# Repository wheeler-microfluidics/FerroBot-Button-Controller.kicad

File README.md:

# FerroBot-Button-Controller.kicad
To control the ferrobot ((https://github.com/wheeler-microfluidics/FerroBot). Firmware here: https://github.com/wheeler-microfluidics/FerroBot-Button-Controller.ino/tree/master

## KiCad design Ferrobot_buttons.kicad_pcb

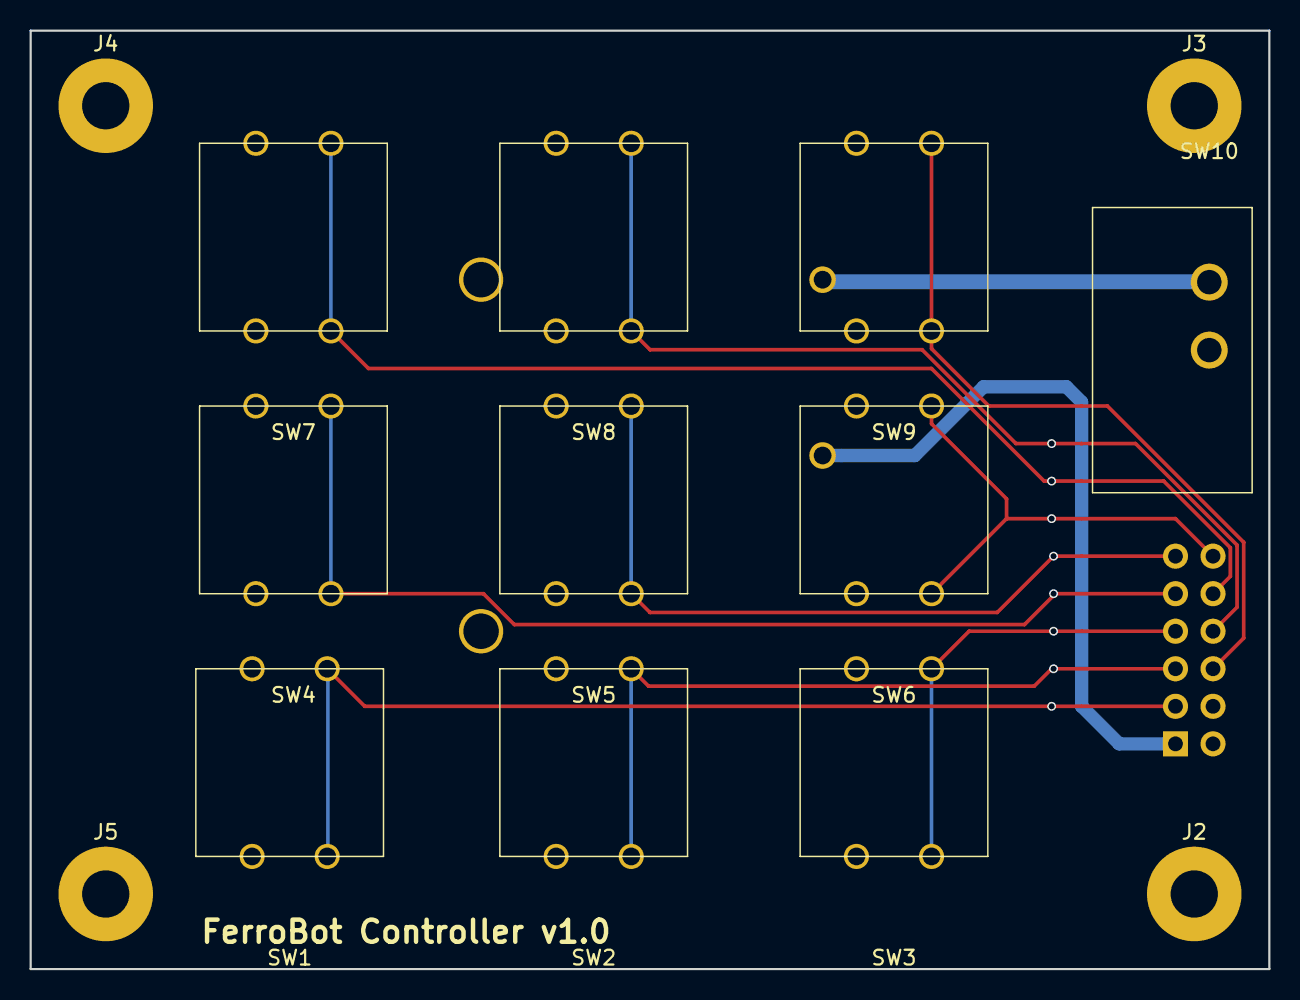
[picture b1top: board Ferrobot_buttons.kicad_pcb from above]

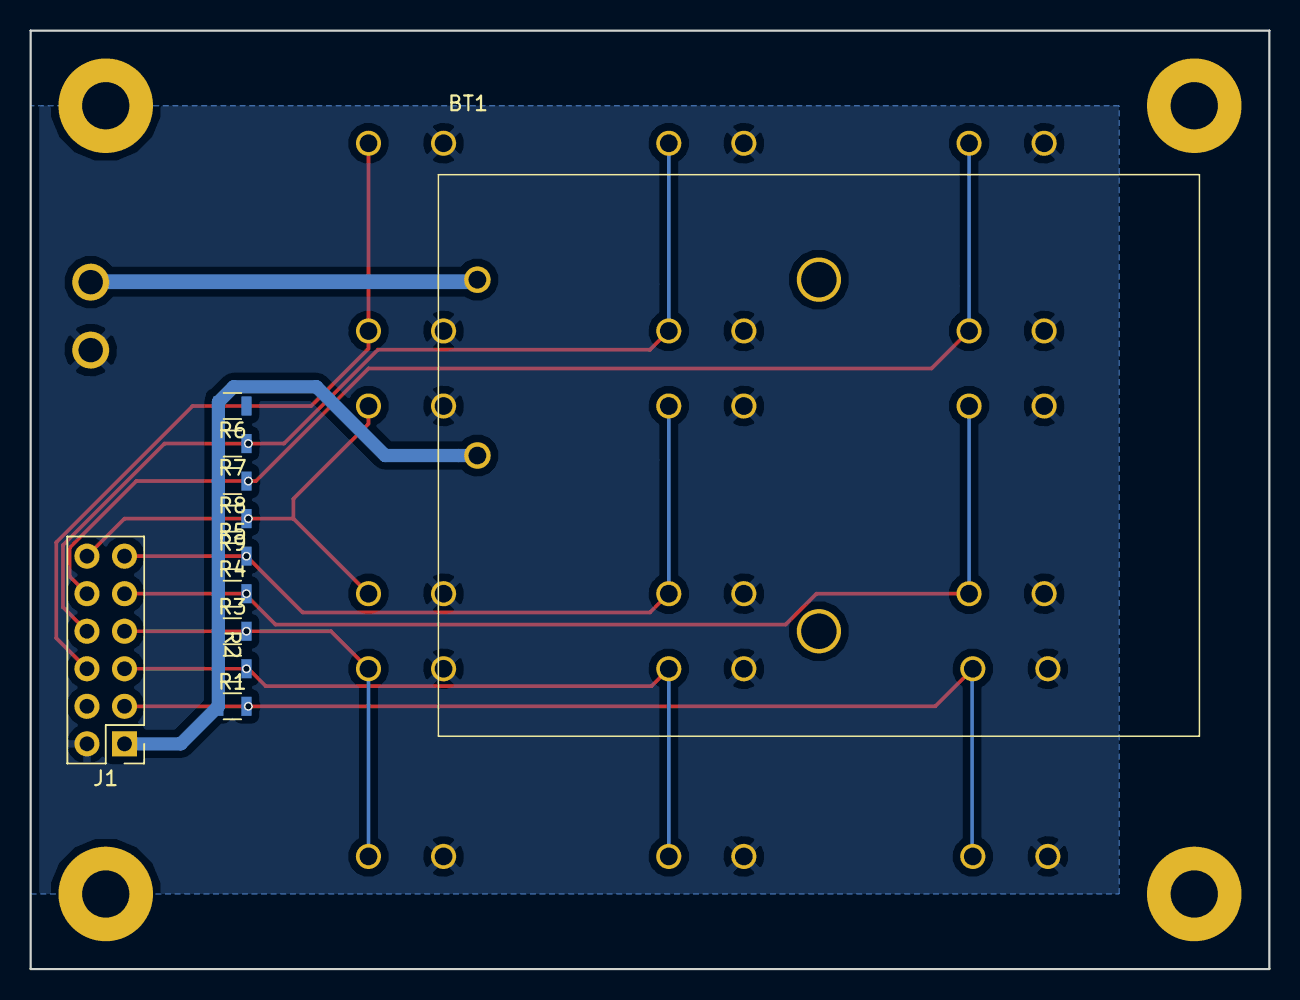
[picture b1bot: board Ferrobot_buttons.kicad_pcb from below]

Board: 2 copper layers, 83.8 x 63.5 mm, 25 parts (11 on the bottom side), 12 nets.

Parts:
BT1: Battery; THREE_AAA_BATTERY_HOLDER
J1: CONN_02X06; Pin_Header_Straight_2x06_Pitch2.54mm
J2, J3, J4, J5: CONN_01X01; MountingHole_3.2mm_M3_Pad
R1, R2, R3, R4, R5, R6, R7, R8, R9: 10k; R_0805
SW1, SW2, SW3, SW4, SW5, SW6, SW7, SW8, SW9: Button; ADAFRUIT_SQUARE_BUTTON
SW10: SW_DIP_x01; L101_Switch

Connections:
BATTERY_OUT: BT1.1, SW10.1
GND: BT1.2, J1.1, R1.1, R2.1, R3.1, R4.1, R5.1, R6.2, R7.2, R8.2, R9.2
MAGNET1: J1.3, R1.2, SW1.2, SW1.4
MAGNET2: J1.5, R2.2, SW2.2, SW2.4
MAGNET3: J1.7, R3.2, SW3.2, SW3.4
MAGNET4: J1.9, R4.2, SW4.2, SW4.4
MAGNET5: J1.11, R5.2, SW5.2, SW5.4
MAGNET6: J1.12, R9.1, SW6.2, SW6.4
MAGNET7: J1.10, R8.1, SW7.2, SW7.4
MAGNET8: J1.8, R7.1, SW8.2, SW8.4
MAGNET9: J1.6, R6.1, SW9.2, SW9.4
PWR: J1.2, SW1.1, SW1.3, SW2.1, SW2.3, SW3.1, SW3.3, SW4.1, SW4.3, SW5.1, SW5.3, SW6.1, SW6.3, SW7.1, SW7.3, SW8.1, SW8.3, SW9.1, SW9.3, SW10.2

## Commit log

2018-05-18 Add pul-down resistors
